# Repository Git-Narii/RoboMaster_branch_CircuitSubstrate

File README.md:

24Vの電源及びCAN通信の信号線を分岐させる基板

4つまでのロボマスモータに対応

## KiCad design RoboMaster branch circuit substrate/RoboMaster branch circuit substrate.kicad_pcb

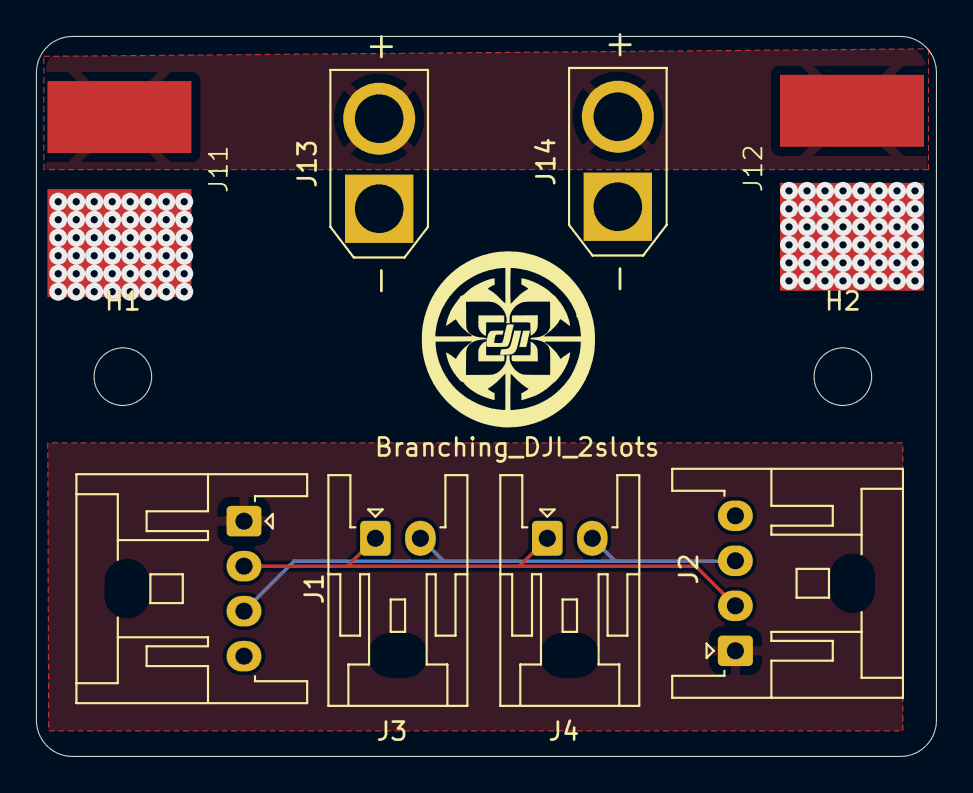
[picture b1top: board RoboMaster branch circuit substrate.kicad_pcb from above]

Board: 2 copper layers, 50.0 x 40.0 mm, 10 parts (0 on the bottom side), 6 nets.

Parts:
H1, H2: MountingHole; MountingHole_3.2mm_M3
J1, J2: Conn_01x04_Socket; JST_XA_S04B-XASK-1_1x04_P2.50mm_Horizontal
J3, J4: Conn_01x02_Socket; JST_XA_S02B-XASK-1_1x02_P2.50mm_Horizontal
J11, J12: Conn_01x02_Socket; xt60
J13, J14: Conn_01x02_Socket; AMASS_XT30U-F_1x02_P5.0mm_Vertical

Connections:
+5V: J1.1, J2.1
/+: J11.2 vcc, J12.2 vcc, J13.2, J14.2
/-: J11.1 GNDA, J12.1 GNDA, J13.1, J14.1
/CANH: J1.2, J2.2, J3.1, J4.1
/CANL: J1.3, J2.3, J3.2, J4.2
GND: J1.4, J2.4
